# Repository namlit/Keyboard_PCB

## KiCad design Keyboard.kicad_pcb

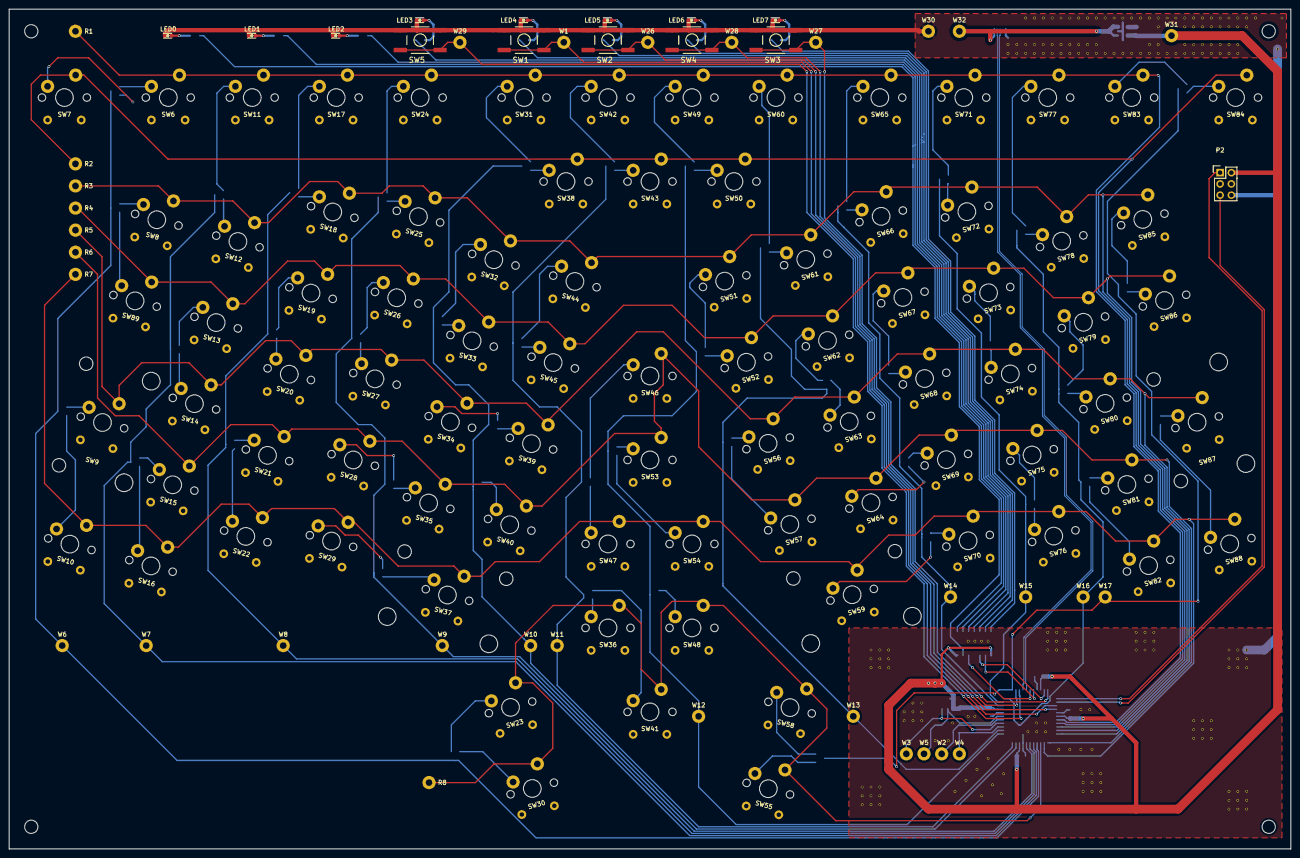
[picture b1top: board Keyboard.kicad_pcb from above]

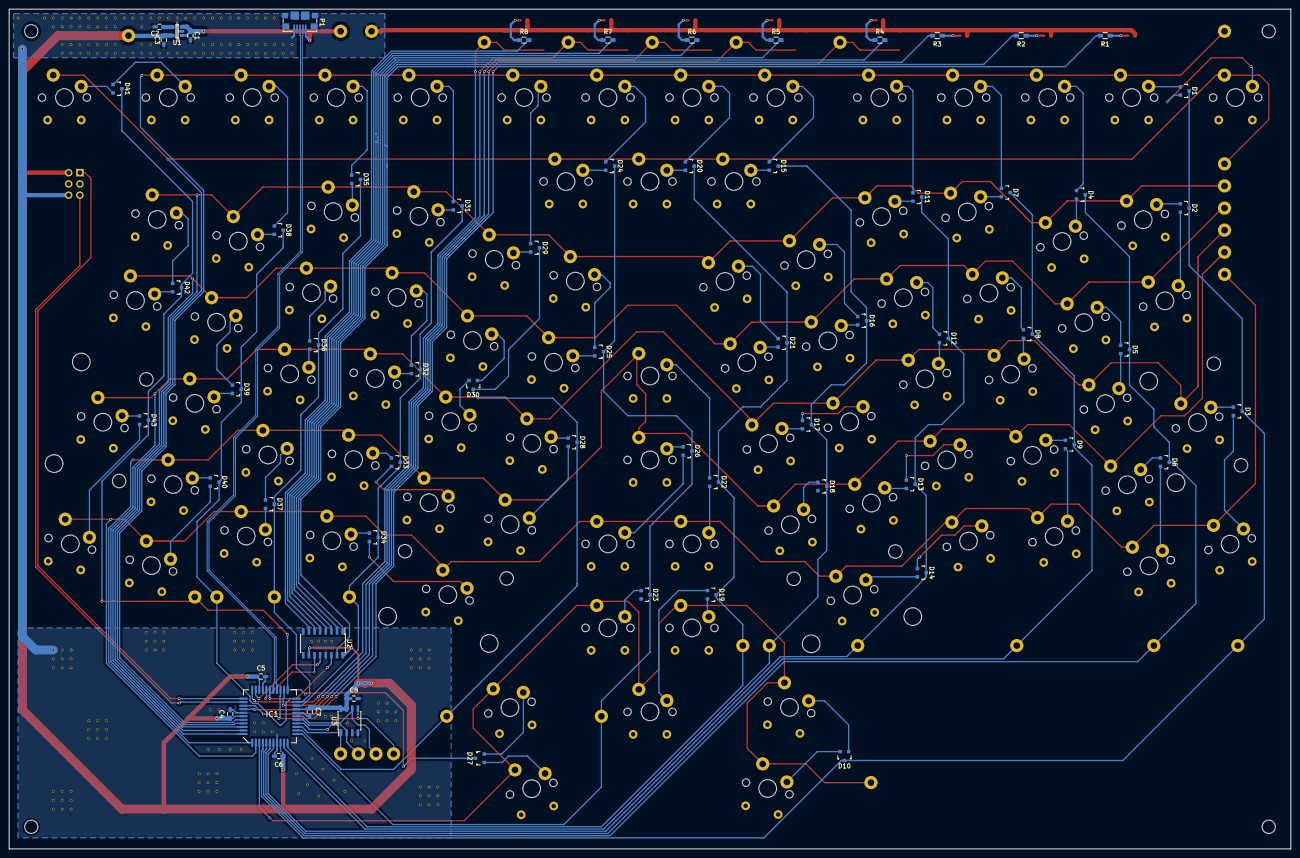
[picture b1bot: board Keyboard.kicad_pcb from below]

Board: 2 copper layers, 290.0 x 190.0 mm, 194 parts (64 on the bottom side), 140 nets.

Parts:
C1, C3: 1u; C_0603_HandSoldering
C2: 10n; C_0603_HandSoldering
C4, C5, C6, C7, C8: 100n; C_0603_HandSoldering
D1, D2, D3, D4, D5, D6, D7, D8, D9, D10, D11, D12, D13, D14, D15, D16, D17, D18, D19, D20, D21, D22, D23, D24, D25, D26, D27, D28, D29, D30, D31, D32, D33, D34, D35, D36, D37, D38, D39, D40, D41, D42, D43: D_Schottky_x2_KCom_AAK; SOT-23
IC1: ATXMEGA128A4U-A; TQFP_44_0.8mmPitch_handSoldering
LED0, LED1, LED2, LED3, LED4, LED5, LED6, LED7: LED; LED_0603
P1: USB_OTG; micro_USB_1981568-1
P2: CONN_PDI; Pin_Header_Straight_2x03
R1, R2, R3, R4, R5, R6, R7, R8: 1k; R_0603_HandSoldering
SW1, SW2, SW3, SW4, SW5: SPST; SPST_TACTM-613N-F
SW6: F1; Cherry_MX
SW7: ESC; Cherry_MX
SW8: head; Cherry_MX
SW9: Shift_L; Cherry_MX_double_vertical
SW10: Strg_L; Cherry_MX
SW11: F2; Cherry_MX
SW12: 1; Cherry_MX
SW13: X; Cherry_MX
SW14: U; Cherry_MX
SW15: Ü; Cherry_MX
SW16: Wind_L; Cherry_MX
SW17: F3; Cherry_MX
SW18: 2; Cherry_MX
SW19: V; Cherry_MX
SW20: I; Cherry_MX
SW21: Ö; Cherry_MX
SW22: Alt_L; Cherry_MX
SW23: M4_L; Cherry_MX
SW24: F4; Cherry_MX
SW25: 3; Cherry_MX
SW26: L; Cherry_MX
SW27: A; Cherry_MX
SW28: Ä; Cherry_MX
SW29: M3_L; Cherry_MX
SW30: M5; Cherry_MX
SW31: F5; Cherry_MX
SW32: 4; Cherry_MX
SW33: C; Cherry_MX
SW34: E; Cherry_MX
SW35: P; Cherry_MX
SW36: Back; Cherry_MX
SW37: enter; Cherry_MX_double_horizontal
SW38: Drucken; Cherry_MX
SW39: O; Cherry_MX
SW40: Z; Cherry_MX
SW41: bottom_middle; Cherry_MX
SW42: F6; Cherry_MX
SW43: Rollen; Cherry_MX
SW44: 5; Cherry_MX
SW45: W; Cherry_MX
SW46: Strg_M; Cherry_MX
SW47: grave; Cherry_MX
SW48: Entf; Cherry_MX
SW49: F7; Cherry_MX
SW50: Pause; Cherry_MX
SW51: 6; Cherry_MX
SW52: K; Cherry_MX
SW53: mitte; Cherry_MX
SW54: aigu; Cherry_MX
SW55: M6; Cherry_MX
SW56: S; Cherry_MX
SW57: B; Cherry_MX
SW58: M4_R; Cherry_MX
SW59: leer; Cherry_MX_double_horizontal
SW60: F8; Cherry_MX
SW61: 7; Cherry_MX
SW62: H; Cherry_MX
SW63: N; Cherry_MX
SW64: M; Cherry_MX
SW65: F9; Cherry_MX
SW66: 8; Cherry_MX
SW67: G; Cherry_MX
SW68: R; Cherry_MX
SW69: komma; Cherry_MX
SW70: M3_R; Cherry_MX
SW71: F10; Cherry_MX
SW72: 9; Cherry_MX
SW73: F; Cherry_MX
SW74: T; Cherry_MX
SW75: punkt; Cherry_MX
SW76: Wind_R; Cherry_MX
SW77: F11; Cherry_MX
SW78: 0; Cherry_MX
SW79: Q; Cherry_MX
SW80: D; Cherry_MX
SW81: J; Cherry_MX
SW82: compose; Cherry_MX
SW83: F12; Cherry_MX
SW84: top_right; Cherry_MX
SW85: minus; Cherry_MX
SW86: ß; Cherry_MX
SW87: Shift_R; Cherry_MX_double_vertical
SW88: bottom_right; Cherry_MX
SW89: Y; Cherry_MX
U1: LDO_3V3_APE8865Y5-33-HF-3TR; SOT-23-5
U2: 74HC595; SOIC-16_3.9x9.9mm_Pitch1.27mm
U3: 25LC256_EEPROM; SOIC-8_3.9x4.9mm_Pitch1.27mm
W1: PR0; Measurement_Point_Round-TH_Big
W2: MISO; Measurement_Point_Round-TH_Big
W3: MOSI; Measurement_Point_Round-TH_Big
W4: ~CS; Measurement_Point_Round-TH_Big
W5: SCK; Measurement_Point_Round-TH_Big
W6: C1; Measurement_Point_Round-TH_Big
W7: C2; Measurement_Point_Round-TH_Big
W8: C3; Measurement_Point_Round-TH_Big
W9: C4; Measurement_Point_Round-TH_Big
W10: C5; Measurement_Point_Round-TH_Big
W11: C6; Measurement_Point_Round-TH_Big
W12: C7; Measurement_Point_Round-TH_Big
W13: C8; Measurement_Point_Round-TH_Big
W14: C9; Measurement_Point_Round-TH_Big
W15: C10; Measurement_Point_Round-TH_Big
W16: C11; Measurement_Point_Round-TH_Big
W17: C12; Measurement_Point_Round-TH_Big
W18: R1; Measurement_Point_Round-TH_Big
W19: R2; Measurement_Point_Round-TH_Big
W20: R3; Measurement_Point_Round-TH_Big
W21: R4; Measurement_Point_Round-TH_Big
W22: R5; Measurement_Point_Round-TH_Big
W23: R6; Measurement_Point_Round-TH_Big
W24: R7; Measurement_Point_Round-TH_Big
W25: R8; Measurement_Point_Round-TH_Big
W26: PR1; Measurement_Point_Round-TH_Big
W27: PE3; Measurement_Point_Round-TH_Big
W28: PD4; Measurement_Point_Round-TH_Big
W29: PD5; Measurement_Point_Round-TH_Big
W30: GND; Measurement_Point_Round-TH_Big
W31: 3V3; Measurement_Point_Round-TH_Big
W32: 5V; Measurement_Point_Round-TH_Big

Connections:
+3V3: C3.1, C4.1, C5.1, C6.1, C7.1, C8.1, IC1.9, IC1.19, IC1.31, IC1.39, P2.2, U1.5, U2.10, U2.16, U3.7, U3.8, W31.1
+5V: C1.1, P1.1, U1.1, U1.3, W32.1
/keyboard_controller/D+: IC1.27, P1.3
/keyboard_controller/D-: IC1.26, P1.2
/keyboard_controller/column_1: D1.3, D2.3, D3.3, D10.3, IC1.4, W6.1
/keyboard_controller/column_2: D4.3, D5.3, D6.3, IC1.5, W7.1
/keyboard_controller/column_3: D7.3, D8.3, D9.3, IC1.6, W8.1
/keyboard_controller/column_4: D11.3, D12.3, D13.3, D14.3, IC1.7, W9.1
/keyboard_controller/column_5: D15.3, D16.3, D17.3, D18.3, IC1.10, W10.1
/keyboard_controller/column_6: D19.3, D20.3, D21.3, D22.3, IC1.11, W11.1
/keyboard_controller/column_7: D23.3, D24.3, D25.3, D26.3, IC1.12, W12.1
/keyboard_controller/column_8: D28.3, D29.3, D30.3, IC1.13, W13.1
/keyboard_controller/column_9: D31.3, D32.3, D33.3, D34.3, IC1.20, W14.1
/keyboard_controller/column_10: D35.3, D36.3, D37.3, IC1.21, W15.1
/keyboard_controller/column_11: D38.3, D39.3, D40.3, IC1.22, W16.1
/keyboard_controller/column_12: D27.3, D41.3, D42.3, D43.3, IC1.23, W17.1
/keyboard_controller/row_1: IC1.40, SW6.2, SW11.2, SW17.2, SW24.2, SW31.2, SW42.2, SW49.2, SW60.2, SW65.2, SW71.2, SW77.2, SW83.2, W18.1
/keyboard_controller/row_2: IC1.41, SW7.2, SW38.2, SW43.2, SW50.2, SW84.2, W19.1
/keyboard_controller/row_3: IC1.42, SW8.2, SW12.2, SW18.2, SW25.2, SW32.2, SW44.2, SW51.2, SW61.2, SW66.2, SW72.2, SW78.2, SW85.2, W20.1
/keyboard_controller/row_4: IC1.43, SW13.2, SW19.2, SW26.2, SW33.2, SW45.2, SW52.2, SW62.2, SW67.2, SW73.2, SW79.2, SW86.2, SW89.2, W21.1
/keyboard_controller/row_5: IC1.44, SW9.2, SW14.2, SW20.2, SW27.2, SW34.2, SW39.2, SW56.2, SW63.2, SW68.2, SW74.2, SW80.2, SW87.2, W22.1
/keyboard_controller/row_6: IC1.1, SW15.2, SW21.2, SW28.2, SW35.2, SW40.2, SW46.2, SW53.2, SW57.2, SW64.2, SW69.2, SW75.2, SW81.2, W23.1
/keyboard_controller/row_7: IC1.2, SW10.2, SW16.2, SW22.2, SW29.2, SW37.2, SW47.2, SW54.2, SW59.2, SW70.2, SW76.2, SW82.2, SW88.2, W24.1
/keyboard_controller/row_8: IC1.3, SW23.2, SW30.2, SW36.2, SW41.2, SW48.2, SW55.2, SW58.2, W25.1
GND: C1.2, C2.2, C3.2, C4.2, C5.2, C6.2, C7.2, C8.2, IC1.8, IC1.18, IC1.30, IC1.38, LED0.1, LED1.1, LED2.1, LED3.1, LED4.1, LED5.1, LED6.1, LED7.1, P1.5, P1.6, P2.6, SW1.1, SW2.1, SW3.1, SW4.1, SW5.1, U1.2, U2.8, U2.13, U3.3, U3.4, W30.1
unnamed: C2.1, U1.4
unnamed: D1.1, SW6.1
unnamed: D1.2, SW7.1
unnamed: D2.1, SW8.1
unnamed: D2.2, SW89.1
unnamed: D3.1, SW9.1
unnamed: D3.2, SW10.1
unnamed: D4.1, SW11.1
unnamed: D4.2, SW12.1
unnamed: D5.1, SW13.1
unnamed: D5.2, SW14.1
unnamed: D6.1, SW15.1
unnamed: D6.2, SW16.1
unnamed: D7.1, SW17.1
unnamed: D7.2, SW18.1
unnamed: D8.1, SW19.1
unnamed: D8.2, SW20.1
unnamed: D9.1, SW21.1
unnamed: D9.2, SW22.1
unnamed: D10.1, SW23.1
unnamed: D10.2, SW30.1
unnamed: D11.1, SW24.1
unnamed: D11.2, SW25.1
unnamed: D12.1, SW26.1
unnamed: D12.2, SW27.1
unnamed: D13.1, SW28.1
unnamed: D13.2, SW35.1
unnamed: D14.1, SW29.1
unnamed: D14.2, SW37.1
unnamed: D15.1, SW31.1
unnamed: D15.2, SW38.1
unnamed: D16.1, SW32.1
unnamed: D16.2, SW33.1
unnamed: D17.1, SW34.1
unnamed: D17.2, SW39.1
unnamed: D18.1, SW40.1
unnamed: D19.1, SW41.1
unnamed: D19.2, SW36.1
unnamed: D20.1, SW42.1
unnamed: D20.2, SW43.1
unnamed: D21.1, SW44.1
unnamed: D21.2, SW45.1
unnamed: D22.1, SW46.1
unnamed: D22.2, SW47.1
unnamed: D23.1, SW48.1
unnamed: D24.1, SW49.1
unnamed: D24.2, SW50.1
unnamed: D25.1, SW51.1
unnamed: D25.2, SW52.1
unnamed: D26.1, SW53.1
unnamed: D26.2, SW54.1
unnamed: D27.1, SW55.1
unnamed: D27.2, SW58.1
unnamed: D28.1, SW56.1
unnamed: D28.2, SW57.1
unnamed: D29.1, SW60.1
unnamed: D29.2, SW61.1
unnamed: D30.1, SW62.1
unnamed: D30.2, SW63.1
unnamed: D31.1, SW65.1
unnamed: D31.2, SW66.1
unnamed: D32.1, SW67.1
unnamed: D32.2, SW68.1
unnamed: D33.1, SW69.1
unnamed: D33.2, SW64.1
unnamed: D34.1, SW70.1
unnamed: D34.2, SW59.1
unnamed: D35.1, SW71.1
unnamed: D35.2, SW72.1
unnamed: D36.1, SW73.1
unnamed: D36.2, SW74.1
unnamed: D37.1, SW75.1
unnamed: D37.2, SW76.1
unnamed: D38.1, SW77.1
unnamed: D38.2, SW78.1
unnamed: D39.1, SW79.1
unnamed: D39.2, SW80.1
unnamed: D40.1, SW81.1
unnamed: D40.2, SW82.1
unnamed: D41.1, SW83.1
unnamed: D41.2, SW84.1
unnamed: D42.1, SW85.1
unnamed: D42.2, SW86.1
unnamed: D43.1, SW87.1
unnamed: D43.2, SW88.1
unnamed: IC1.14, U3.1, W4.1
unnamed: IC1.15, U3.5, W3.1
unnamed: IC1.16, U3.2, W2.1
unnamed: IC1.17, U3.6, W5.1
unnamed: IC1.24, SW4.2, W28.1
unnamed: IC1.25, SW5.2, W29.1
unnamed: IC1.28, U2.14
unnamed: IC1.29, U2.11
unnamed: IC1.32, U2.12
unnamed: IC1.33, SW3.2, W27.1
unnamed: IC1.34, P2.1
unnamed: IC1.35, P2.5
unnamed: IC1.36, SW1.2, W1.1
unnamed: IC1.37, SW2.2, W26.1
unnamed: LED0.2, R1.1
unnamed: LED1.2, R2.1
unnamed: LED2.2, R3.1
unnamed: LED3.2, R4.1
unnamed: LED4.2, R5.1
unnamed: LED5.2, R6.1
unnamed: LED6.2, R7.1
unnamed: LED7.2, R8.1
unnamed: R1.2, U2.15
unnamed: R2.2, U2.1
unnamed: R3.2, U2.2
unnamed: R4.2, U2.3
unnamed: R5.2, U2.4
unnamed: R6.2, U2.5
unnamed: R7.2, U2.6
unnamed: R8.2, U2.7

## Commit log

2016-03-09 Add Gerbers sended to manufacturer
